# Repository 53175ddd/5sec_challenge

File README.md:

# 5sec_challenge

[#5sec_challenge](https://x.com/hashtag/5sec_challenge) とは：あなたの体内時計がどれほど正確か / いい加減かを試すことができる挑戦です

# 組み立て例

こんな感じに組み上がります．  
Arduino Nano は互換品を使っています．

# Booth 販売ページ

<https://nch-mosfet.booth.pm/items/6582794>

こんなのが届きます．

これに追加で，Arduino Nano をご用意下さい．Amazon で買える適当なもので大丈夫です．

# 簡易組み立て手順書

1. 部品をはんだ付けする
2. Arduino Nano にプログラムを書き込む
3. 組み上げる
4. 動かす

## 部品をはんだ付けする

基本的にフットプリントの通りのものをはんだ付けして行きます．  
向きは下の画像を参考にして下さい．C1 / C2 については，C1 が 104，C2 が 224 です．

## Arduino Nano にプログラムを書き込む

適合する USB ケーブルを使って PC に接続し，[5sec_challenge.ino](./5sec_challenge.ino) を書き込んで下さい．

## 組み上げる

トップ画像を参考に組み上げて下さい．スイッチを接続するかは任意です．

## 動かす

電源（USB または DC9 ~ 12V）を接続し，スイッチ（SW1）をぽちぽちしてください．結果が表示されます．  
その後，スイッチ（SW1）を押しながら Arduino Nano をリセットし，サブモードで起動させて下さい．スイッチを長押しして，タイムが常時表示されるようになれば動作確認完了です．

# 遊び方

友達や家族，知り合いなどと一緒に，誰が一番 5.000 秒に近いスコアを出せるかを勝負するもよし，一人で黙々とトライするもよし，9.999 秒までしか測れないストップウォッチとして使うもよし（？）  
結果はぜひ [#5sec_challenge](https://x.com/hashtag/5sec_challenge) を添えてツイートしてください．

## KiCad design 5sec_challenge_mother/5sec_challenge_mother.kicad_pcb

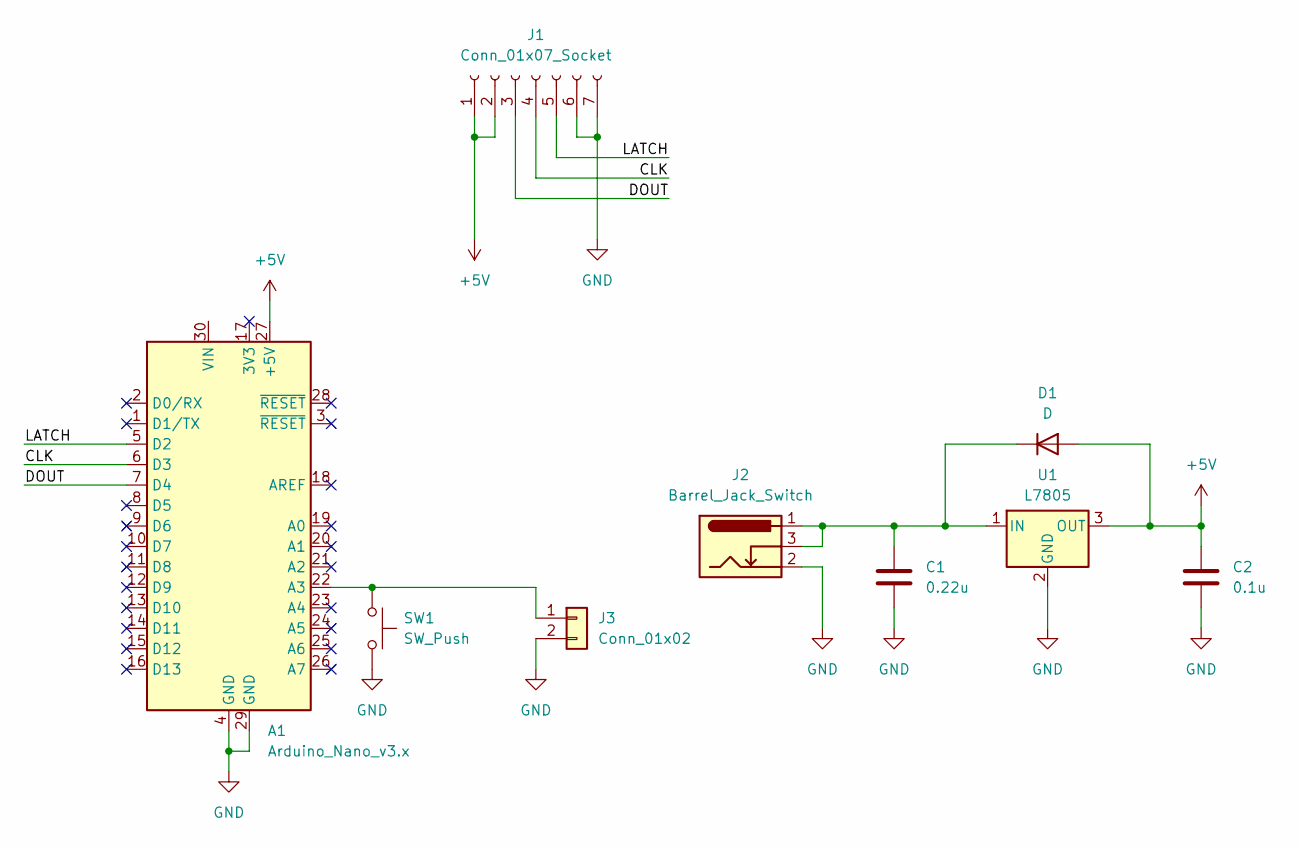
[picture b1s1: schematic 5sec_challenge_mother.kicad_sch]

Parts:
A1: Arduino_Nano_v3.x; Arduino_Nano
C1: 0.22u; C_Disc_D4.7mm_W2.5mm_P5.00mm
C2: 0.1u; C_Disc_D4.7mm_W2.5mm_P5.00mm
D1: D; D_A-405_P10.16mm_Horizontal
J1: Conn_01x07_Socket; PinSocket_1x07_P2.54mm_Vertical
J2: Barrel_Jack_Switch; BarrelJack_Horizontal
J3: Conn_01x02; JST_XH_B2B-XH-AM_1x02_P2.50mm_Vertical
SW1: SW_Push; SW_PUSH_6mm
U1: L7805; TO-220-3_Vertical

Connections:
+5V: A1.27 (+5V), C2.2, D1.2 (A), J1.1, J1.2, U1.3 (OUT)
/CLK: A1.6 (D3), J1.4
/DOUT: A1.7 (D4), J1.3
/LATCH: A1.5 (D2), J1.5
GND: A1.4 (GND), A1.29 (GND), C1.2, C2.1, J1.6, J1.7, J2.2, J3.2, SW1.2, U1.2 (GND)
unnamed: A1.22 (A3), J3.1, SW1.1
unnamed: C1.1, D1.1 (K), J2.1, J2.3, U1.1 (IN)

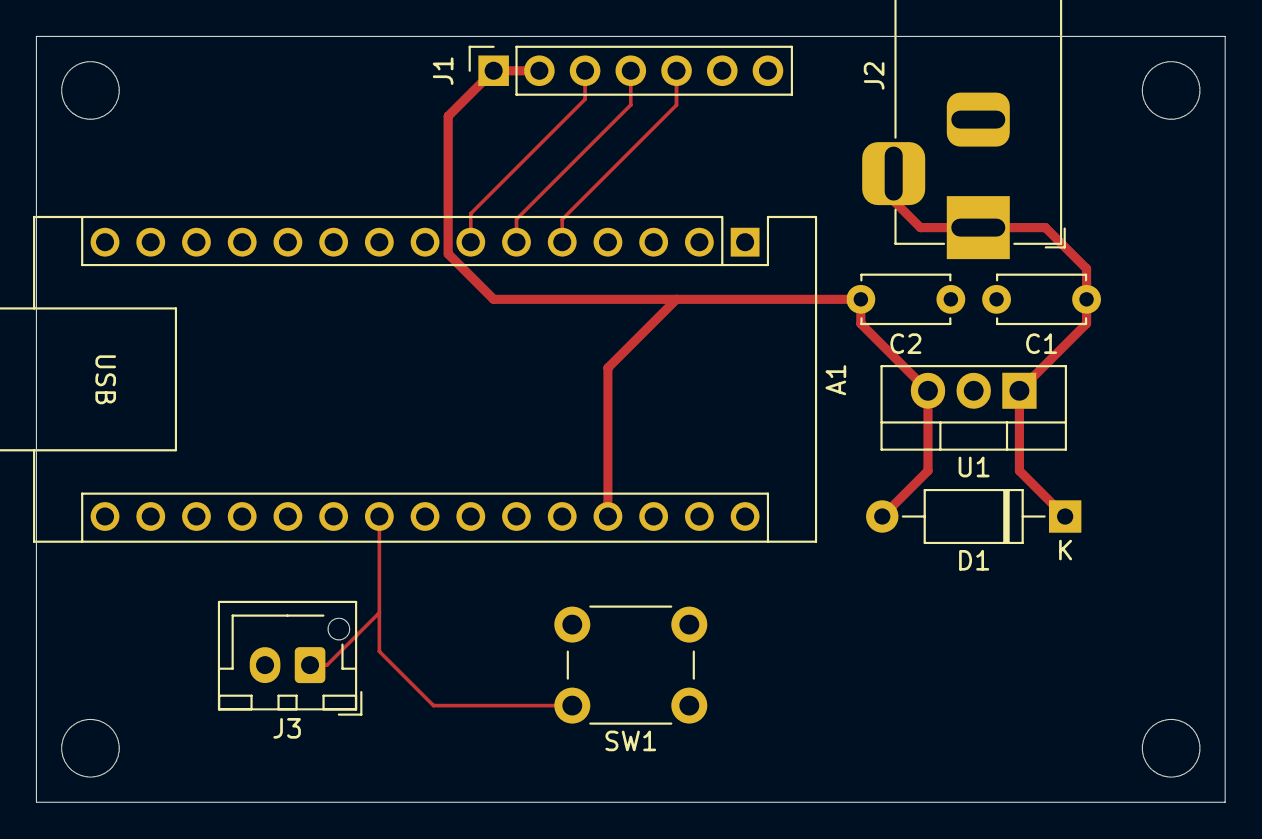
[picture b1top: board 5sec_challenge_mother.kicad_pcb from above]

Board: 2 copper layers, 66.0 x 42.5 mm, 9 parts (0 on the bottom side), 7 nets.

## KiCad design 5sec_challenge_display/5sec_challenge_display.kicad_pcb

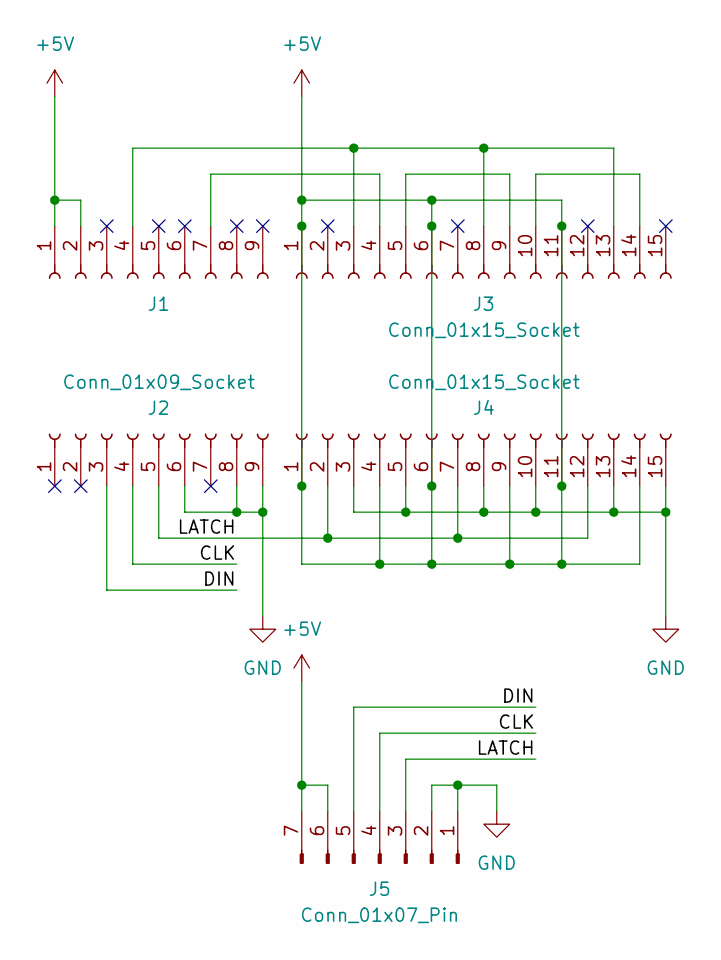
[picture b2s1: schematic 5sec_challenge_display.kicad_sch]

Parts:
J1, J2: Conn_01x09_Socket; PinSocket_1x09_P2.54mm_Vertical
J3, J4: Conn_01x15_Socket; PinSocket_1x15_P2.54mm_Vertical
J5: Conn_01x07_Pin; PinHeader_1x07_P2.54mm_Horizontal

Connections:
+5V: J1.1, J1.2, J3.1, J3.6, J3.11, J4.1, J4.4, J4.6, J4.9, J4.11, J4.14, J5.6, J5.7
/CLK: J2.4, J5.4
/DIN: J2.3, J5.5
/LATCH: J2.5, J4.2, J4.7, J4.12, J5.3
GND: J2.6, J2.8, J2.9, J4.3, J4.5, J4.8, J4.10, J4.13, J4.15, J5.1, J5.2
unnamed: J1.4, J3.3, J3.8, J3.13
unnamed: J1.7, J3.4
unnamed: J3.5, J3.9
unnamed: J3.10, J3.14

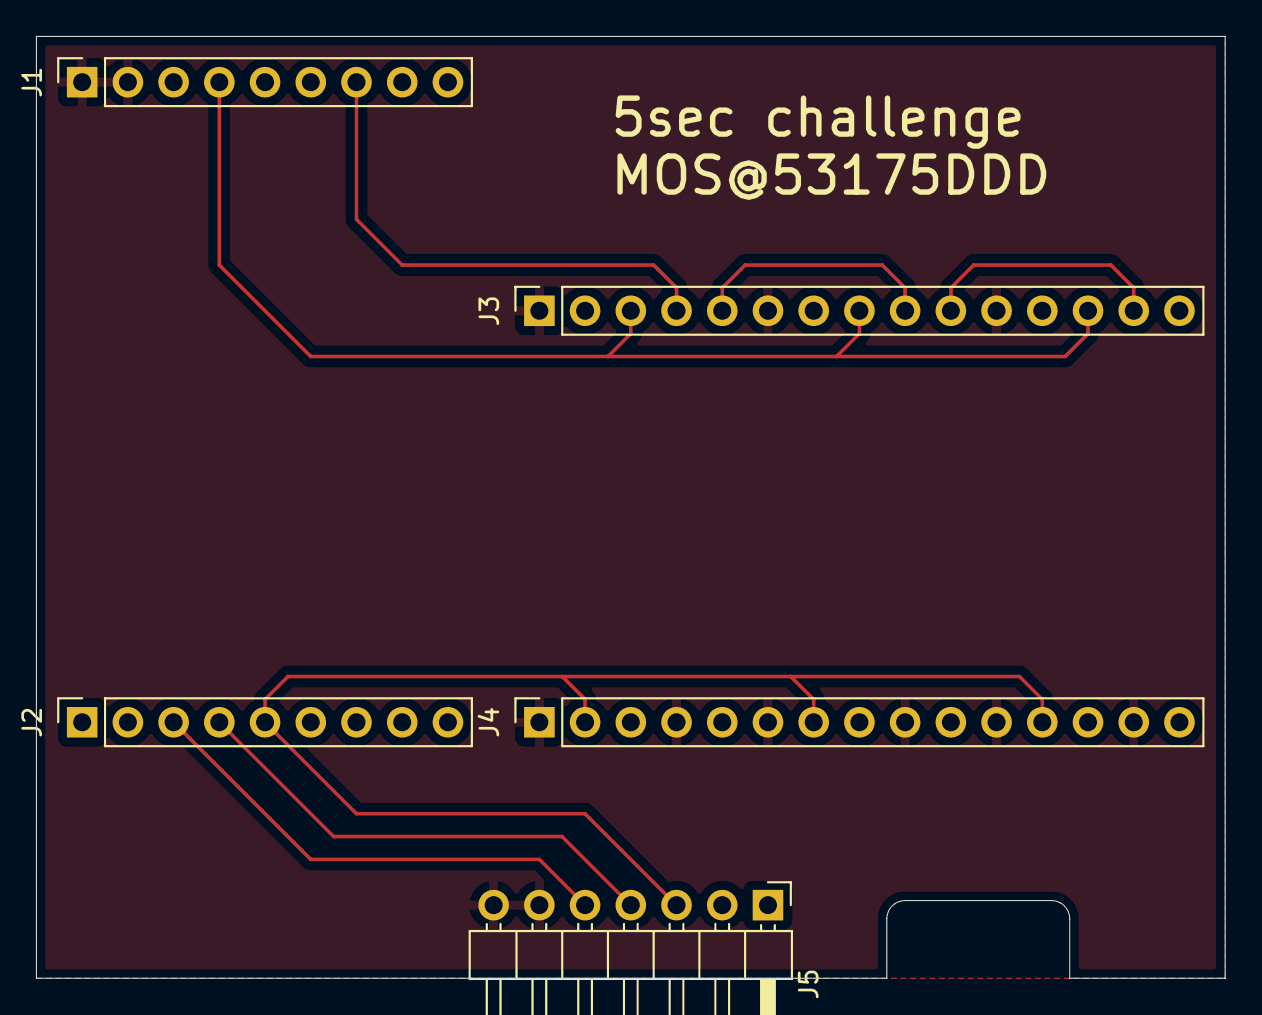
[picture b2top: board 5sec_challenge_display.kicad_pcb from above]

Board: 2 copper layers, 66.0 x 52.3 mm, 5 parts (0 on the bottom side), 9 nets.

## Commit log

2025-01-10 Arduino プロジェクト作成
2025-01-10 コード整形
2025-01-11 KiCAD プロジェクト作成
2025-01-13 一旦削除（作り直し）
2025-01-13 KiCAD プロジェクト作り直し
2025-01-13 表示基板作成
2025-01-14 基板外形調整
2025-01-14 ガーバー出力
2025-01-14 スイッチ付け忘れてたので追加
2025-01-14 スイッチ追加
2025-01-28 ほぼ完成
2025-02-03 モード追加
    スイッチを押しながら起動するとモード切替
2025-03-19 起動時に 5.000 を表示するように変更
